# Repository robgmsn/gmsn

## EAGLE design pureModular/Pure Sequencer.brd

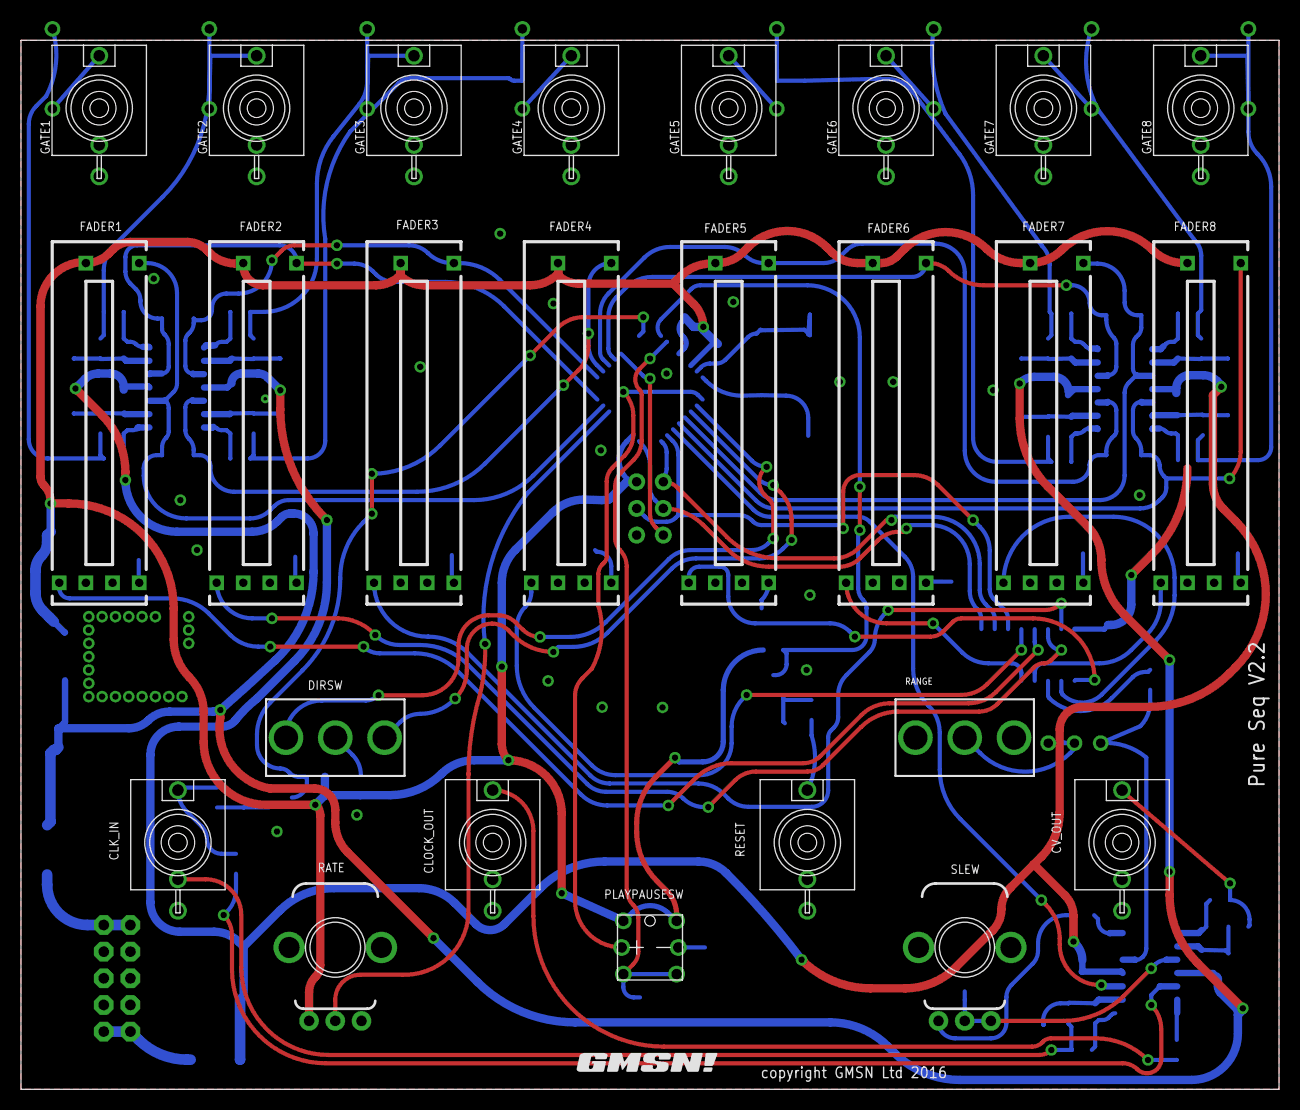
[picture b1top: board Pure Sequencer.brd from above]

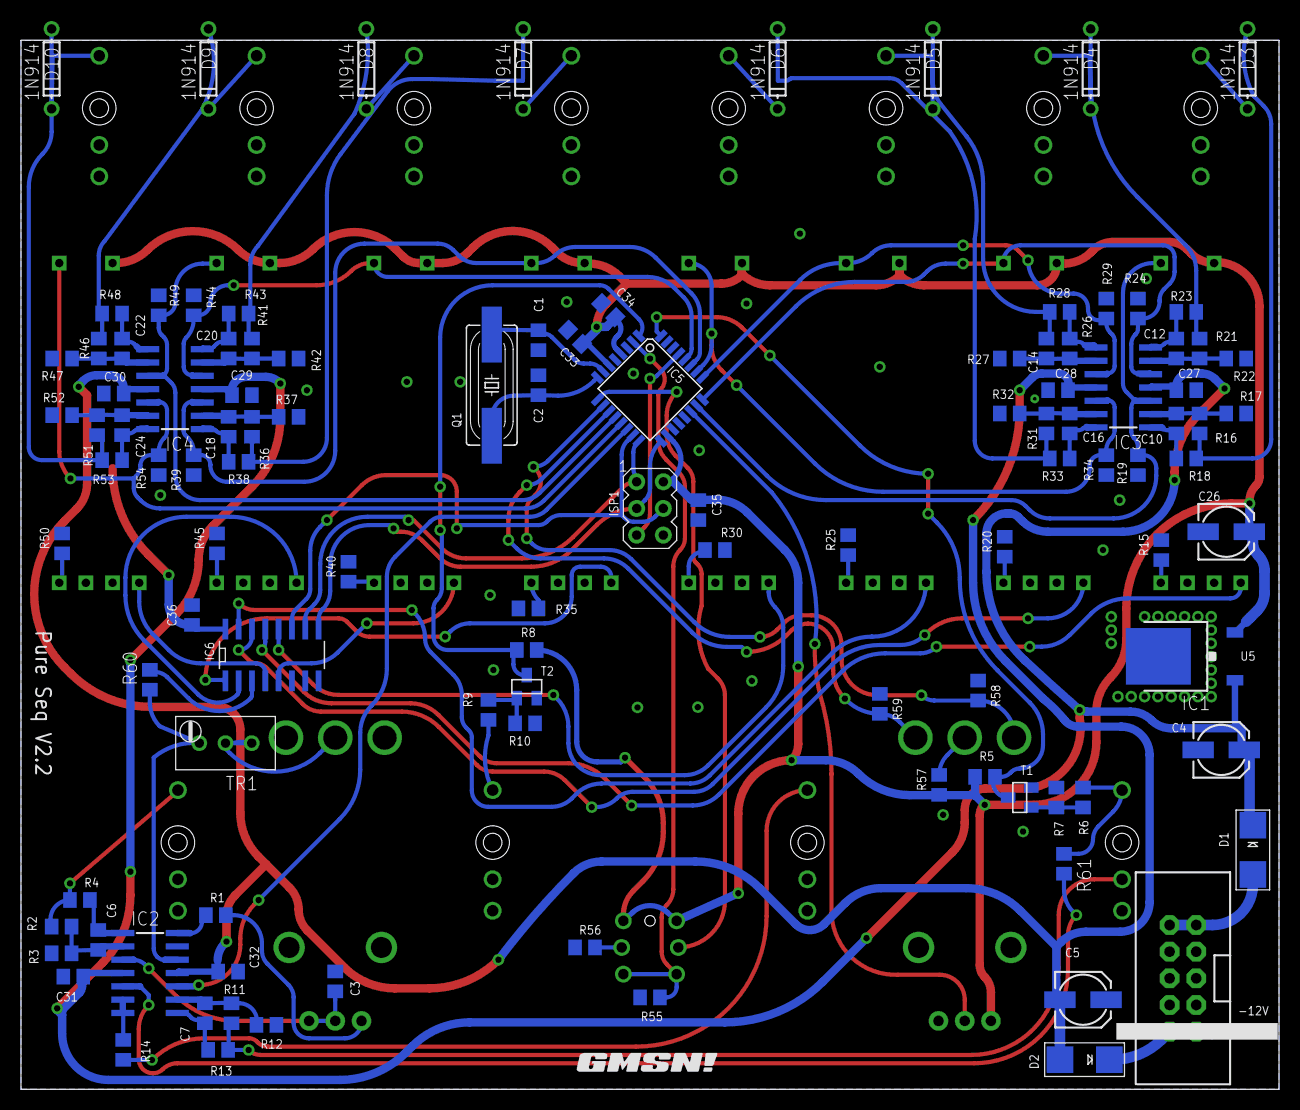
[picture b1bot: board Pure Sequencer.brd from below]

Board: 2 copper layers, 119.9 x 100.0 mm, 136 parts (110 on the bottom side), 97 nets.

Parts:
C1, C2: 22pF; C0805
C3: 1u; C0805
C4, C5, C26: 10uF; 153CLV-0505
C6, C7: 47pF; C0805
C10, C12, C14, C16, C18, C20, C22, C24: 100pF; C0805
C27, C28, C29, C30, C31, C32, C33, C34, C35, C36: 100nF; C0805
CLK_IN: PJ301M-12
CLOCK_OUT: PJ301M-12
CV_OUT: PJ301M-12
D1, D2: STTH102A; SMADIODE
D3, D4, D5, D6, D7, D8, D9, D10: 1N914; DO-41
DIRSW: SWITCH_TOGGLE; TOGGLE_SW
FADER1, FADER2, FADER3, FADER4, FADER5, FADER6, FADER7, FADER8: 100k; FADER_20MM_LED
GATE1, GATE2, GATE3, GATE4, GATE5, GATE6, GATE7, GATE8: PJ301M-12
GLIDE: B100k; POTENTIOMETER_9MM
IC1: BA178M05FP; TO252
IC2, IC3, IC4: TL074; SO14
IC5: ATMEGA328P; TQFP32-08
IC6: CD4051; SOIC_16
ISP1: HEADER2X3-6; AVRISP
JP1: HEADER2X5SHD; 2X5-SHROUDED
Q1: 20MHz; HC49UP
R1, R4: 0R; R0805
R2: 34k; R0805
R3: 56k; R0805
R5, R8: 10k; R0805
R6, R9, R11, R12, R16, R17, R19, R21, R22, R24, R26, R27, R29, R31, R32, R34, R36, R37, R39, R41, R42, R44, R46, R47, R49, R51, R52, R54, R55, R58, R59, R61: 100k; R0805
R7, R10: 1M; R0805
R13, R14, R18, R23, R28, R33, R38, R43, R48, R53, R57: 1k; R0805
R15, R20, R25, R30, R35, R40, R45, R50, R56: 330R; R0805
R60: 200k; R0805
RANGE: SWITCH_TOGGLE; TOGGLE_SW
RATE: B100k; POTENTIOMETER_9MM
RESET: PJ301M-12
SW1: PB6149L
T1, T2: MMBT3904; SOT23
TR1: 100k; TRIMMER_TH
U$1, U$2: GMSN!_LOGO

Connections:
5V: C26.+, C33.1, C34.1, C35.1, C36.1, FADER1.1, FADER2.1, FADER3.1, FADER4.1, FADER5.1, FADER6.1, FADER7.1, FADER8.1, IC1.2, IC5.4, IC5.6, IC5.18, IC6.16, ISP1.2, R5.2, R8.2, R57.1, RATE.P$1, SW1.3, SW1.4
+12V: C4.+, C27.1, C29.1, C31.1, D1.C, IC1.1, IC2.4, IC3.4, IC4.4
-12V: C5.-, C28.2, C30.2, C32.2, D2.A, IC2.11, IC3.11, IC4.11
A: IC5.15, IC6.11, ISP1.4
B: IC5.16, IC6.10, ISP1.1
C: IC5.17, IC6.9, ISP1.3
CLK_IN: IC5.32, R5.1, T1.3
CLK_OUT: IC2.10, IC5.14
G0: FADER1.A, IC3.3, IC5.23, R19.2
G1: FADER2.A, IC3.5, IC5.24, R24.2
G2: FADER3.A, IC3.10, IC5.25, R29.2
G3: FADER4.A, IC3.12, IC5.26, R34.2
G4: FADER5.A, IC4.3, IC5.27, R39.2
G5: FADER6.A, IC4.5, IC5.28, R44.2
G6: FADER7.A, IC4.10, IC5.12, R49.2
G7: FADER8.A, IC4.12, IC5.13, R54.2
GND: C1.2, C2.2, C3.2, C4.-, C5.+, C26.-, C27.2, C28.1, C29.2, C30.1, C31.2, C32.1, C33.2, C34.2, C35.2, C36.2, CLK_IN.GND, CLOCK_OUT.GND, CV_OUT.GND, FADER1.3, FADER2.3, FADER3.3, FADER4.3, FADER5.3, FADER6.3, FADER7.3, FADER8.3, GATE1.GND, GATE2.GND, GATE3.GND, GATE4.GND, GATE5.GND, GATE6.GND, GATE7.GND, GATE8.GND, IC1.3, IC5.3, IC5.5, IC5.21, IC6.6, IC6.7, IC6.8, ISP1.6, JP1.3, JP1.4, JP1.5, JP1.6, JP1.7, JP1.8, R3.1, R7.1, R10.1, R12.2, R15.2, R17.1, R19.1, R20.2, R22.1, R24.1, R25.2, R27.1, R29.1, R30.2, R32.1, R34.1, R35.2, R37.1, R39.1, R40.2, R42.1, R44.1, R45.2, R47.1, R49.1, R50.2, R52.1, R54.1, R55.1, R56.1, R58.1, R59.1, RANGE.3, RATE.P$3, RESET.GND, T1.2, T2.2
unnamed: C1.1, IC5.7, Q1.2
unnamed: C2.1, IC5.8, Q1.1
unnamed: IC2.12, R60.1, TR1.1
unnamed: IC2.13, IC2.14, R1.1
unnamed: GLIDE.P$1, R1.2
unnamed: FADER8.2, IC6.4
unnamed: FADER7.2, IC6.2
unnamed: FADER6.2, IC6.5
unnamed: D1.A, JP1.9, JP1.10
unnamed: D2.C, JP1.1, JP1.2
unnamed: FADER5.2, IC6.1
unnamed: FADER4.2, IC6.12
unnamed: FADER3.2, IC6.15
unnamed: FADER2.2, IC6.14
unnamed: FADER1.2, IC6.13
unnamed: C3.1, GLIDE.P$2, GLIDE.P$3, IC2.3
unnamed: R6.1, R7.2, T1.1
unnamed: IC2.5, R61.2
unnamed: C6.1, IC2.2, R2.1, R3.2
unnamed: C6.2, IC2.1, R4.1
unnamed: CV_OUT.TIP, R2.2, R4.2
unnamed: R9.1, R10.2, T2.1
unnamed: R9.2, RESET.TIP
unnamed: C7.1, IC2.9, R11.2, R12.1
unnamed: C7.2, IC2.8, R13.2
unnamed: CLK_IN.TIP, R6.2, R61.1
unnamed: IC2.6, IC2.7, R14.2
unnamed: CLOCK_OUT.TIP, R14.1
unnamed: CLK_IN.NORM, R11.1, R13.1
unnamed: IC5.22, RATE.P$2
unnamed: FADER1.K, R15.1
unnamed: C10.1, IC3.2, R16.1, R17.2
unnamed: C10.2, IC3.1, R18.1
unnamed: D3.A, R16.2, R18.2
unnamed: FADER3.K, R25.1
unnamed: FADER2.K, R20.1
unnamed: C12.1, IC3.6, R21.1, R22.2
unnamed: C12.2, IC3.7, R23.1
unnamed: D4.A, R21.2, R23.2
unnamed: C14.1, IC3.9, R26.1, R27.2
unnamed: C14.2, IC3.8, R28.1
unnamed: D5.A, R26.2, R28.2
unnamed: FADER4.K, R30.1
unnamed: C16.1, IC3.13, R31.1, R32.2
unnamed: C16.2, IC3.14, R33.1
unnamed: D6.A, R31.2, R33.2
unnamed: FADER5.K, R35.1
unnamed: C18.1, IC4.2, R36.1, R37.2
unnamed: C18.2, IC4.1, R38.1
unnamed: D7.A, R36.2, R38.2
unnamed: FADER6.K, R40.1
unnamed: C20.1, IC4.6, R41.1, R42.2
unnamed: C20.2, IC4.7, R43.1
unnamed: D8.A, R41.2, R43.2
unnamed: FADER7.K, R45.1
unnamed: C22.1, IC4.9, R46.1, R47.2
unnamed: C22.2, IC4.8, R48.1
unnamed: D9.A, R46.2, R48.2
unnamed: FADER8.K, R50.1
unnamed: C24.1, IC4.13, R51.1, R52.2
unnamed: C24.2, IC4.14, R53.1
unnamed: D10.A, R51.2, R53.2
unnamed: IC5.2, R55.2, SW1.1, SW1.2
unnamed: IC5.9, SW1.A
unnamed: R56.2, SW1.K
unnamed: DIRSW.2, R57.2
unnamed: DIRSW.1, IC5.10, R58.2
unnamed: DIRSW.3, IC5.11, R59.2
unnamed: IC6.3, R60.2
unnamed: RANGE.2, TR1.2, TR1.3
unnamed: D6.C, GATE4.TIP
unnamed: D5.C, GATE3.TIP
unnamed: D4.C, GATE2.TIP
unnamed: D3.C, GATE1.TIP
unnamed: D10.C, GATE8.TIP
unnamed: D9.C, GATE7.TIP
unnamed: D8.C, GATE6.TIP
unnamed: D7.C, GATE5.TIP
RESET: IC5.1, R8.1, T2.3
RST: IC5.29, ISP1.5

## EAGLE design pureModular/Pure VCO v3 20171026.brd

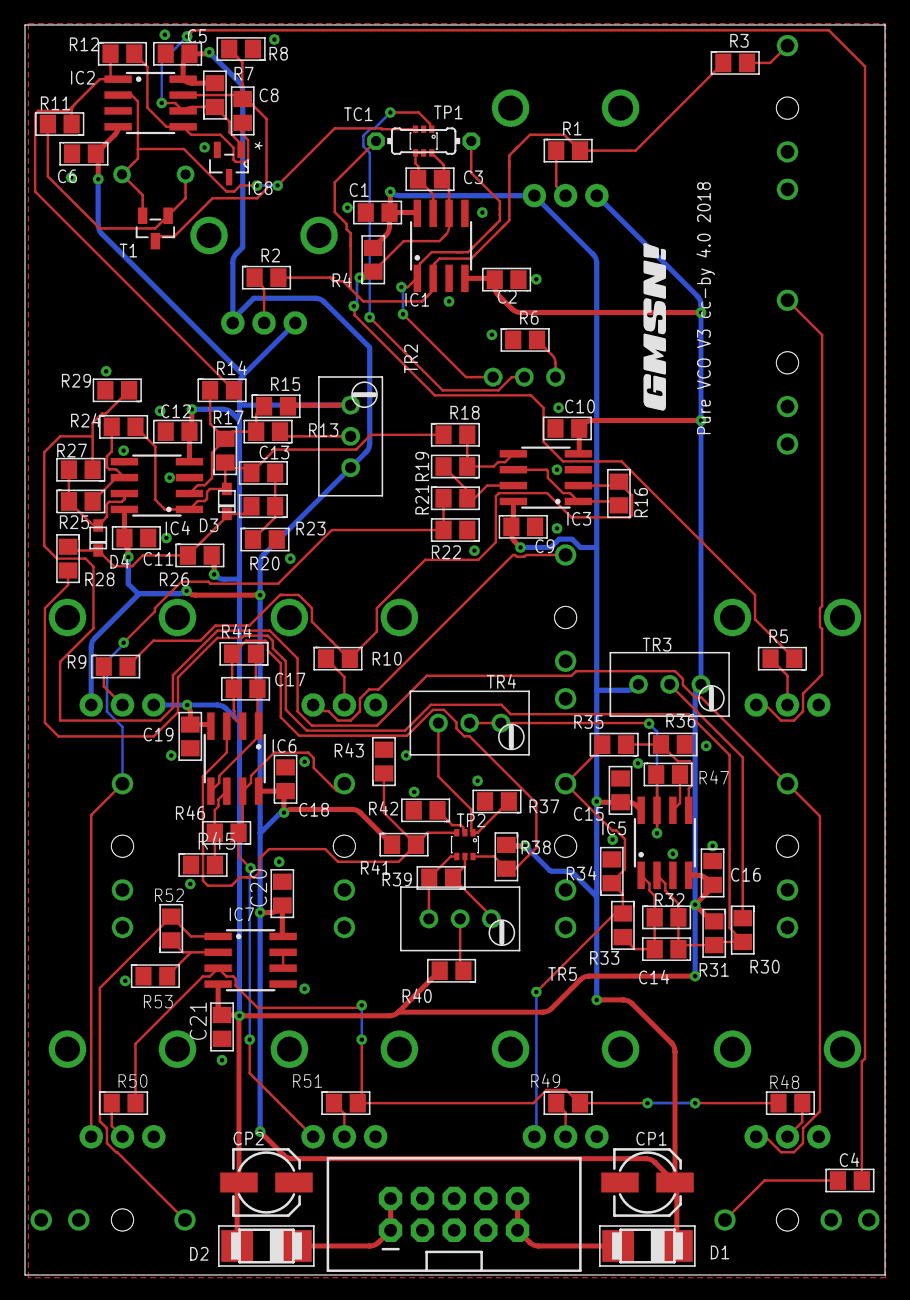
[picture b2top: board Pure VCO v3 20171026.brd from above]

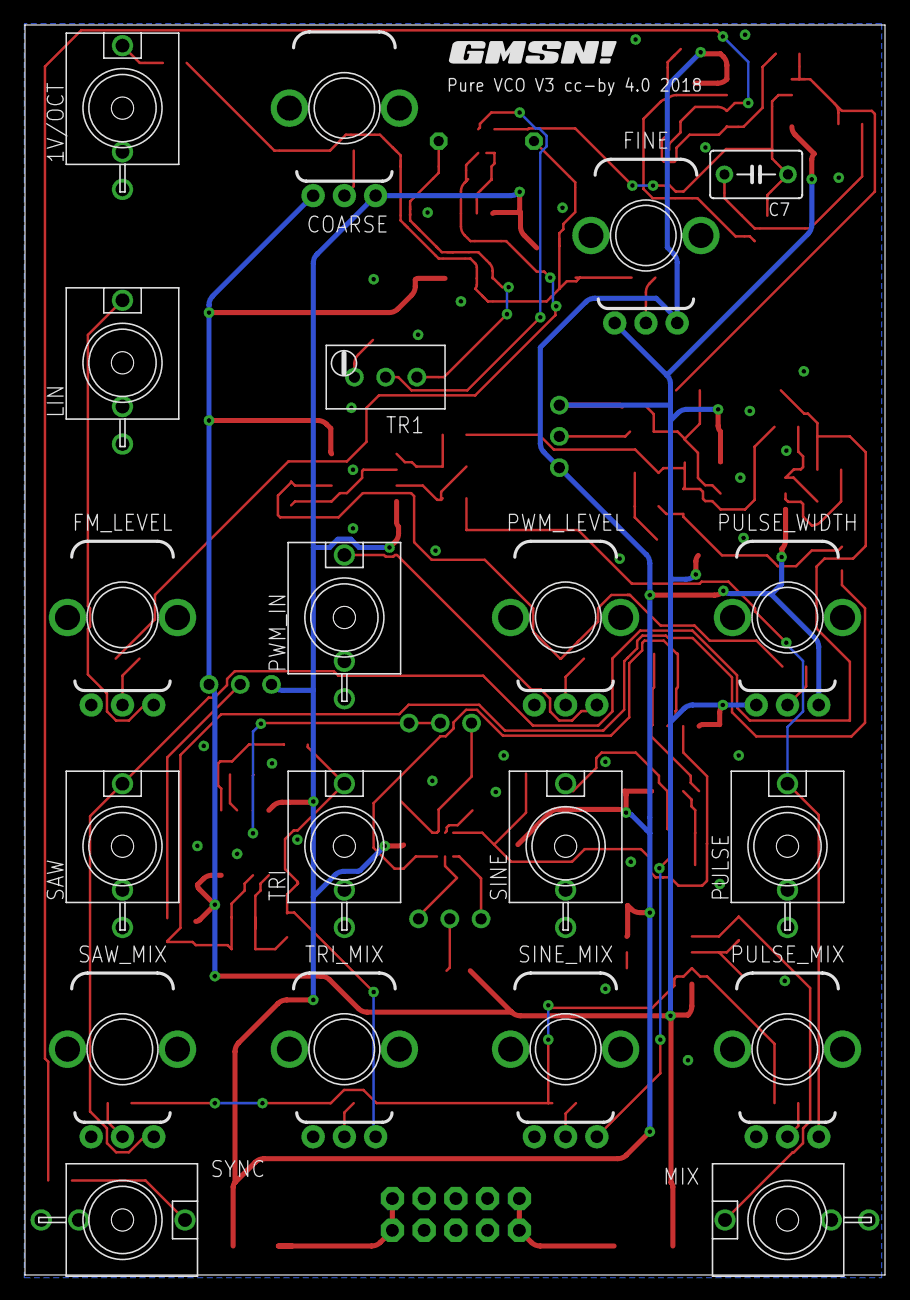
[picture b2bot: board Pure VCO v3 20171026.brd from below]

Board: 2 copper layers, 68.8 x 100.0 mm, 118 parts (21 on the bottom side), 64 nets.

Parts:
1V/OCT: PJ301M-12
C1, C2, C5, C6, C9, C10, C11, C12, C15, C16, C18, C19, C20, C21: 100nF; C0805
C3, C4, C17: 100pF; C0805
C7: 2.2nF; POLY_CAP
C8: 22pF; C0805
C13: 10nF; C0805
C14: 1nF; C0805
COARSE: B100k; POTENTIOMETER_9MM
CP1, CP2: 10uF; 153CLV-0505
D1, D2: STTH102A; SMADIODE
D3, D4: 1N914; SOD-323F
FINE: B100k; POTENTIOMETER_9MM
FM_LEVEL: B100k; POTENTIOMETER_9MM
IC1, IC2, IC3, IC4, IC5, IC6, IC7: TL072; SO08
IC8: LM4040A50IDBZT; SOT95P237X112-3N
JP1: HEADER2X5SHD; 2X5-SHROUDED
LIN: PJ301M-12
MIX: PJ301M-12
PULSE: PJ301M-12
PULSE_MIX: B100k; POTENTIOMETER_9MM
PULSE_WIDTH: B100k; POTENTIOMETER_9MM
PWM_IN: PJ301M-12
PWM_LEVEL: B100k; POTENTIOMETER_9MM
R1: 150k; R0805
R2: 2M2; R0805
R3, R16, R30, R48, R49, R50, R51, R52, R53: 100k; R0805
R4, R19: 2M; R0805
R5: 560k; R0805
R6: 390R; R0805
R7: 87k; R0805
R8, R36: 3k3; R0805
R9: 120k; R0805
R10, R17: 39k; R0805
R11: 680R; R0805
R12: 9k1; R0805
R13: 5k6; R0805
R14, R20, R23, R28, R38, R40, R41, R43, R44, R45: 10k; R0805
R15: 56k; R0805
R18: 2k2; R0805
R21, R22: 1k5; R0805
R24, R25: 22k; R0805
R26, R32, R46: 19k1; R0805
R27, R29, R34, R37, R42: 2k; R0805
R31: 27k; R0805
R33, R35, R47: 1k3; R0805
R39: 402R; R0805
SAW: PJ301M-12
SAW_MIX: B100k; POTENTIOMETER_9MM
SINE: PJ301M-12
SINE_MIX: B100k; POTENTIOMETER_9MM
SYNC: PJ301M-12
T1: MMBFJ309; N_CHN
TC1: 2k; 0204/7
TP1, TP2: DMMT3904W-7-F; TRANS_PAIR
TR1: 100R; TRIMMER_TH
TR2, TR3, TR4, TR5: 100k; TRIMMER_TH
TRI: PJ301M-12
TRI_MIX: B100k; POTENTIOMETER_9MM
U$1, U$2: GMSN!_LOGO

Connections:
+12V: C1.1, C5.1, C9.1, C11.1, C15.1, C18.1, C20.1, COARSE.P$3, CP1.+, D1.C, FINE.P$3, IC1.8, IC2.8, IC3.8, IC4.8, IC5.8, IC6.8, IC7.8, PULSE_WIDTH.P$3, R4.2, R7.2, R38.1, R41.1, TR2.3, TR3.3
-12V: C2.2, C6.2, C10.2, C12.2, C16.2, C19.2, C21.2, COARSE.P$1, CP2.-, D2.A, FINE.P$1, IC1.4, IC2.4, IC3.4, IC4.4, IC5.4, IC6.4, IC7.4, PULSE_WIDTH.P$1, R15.2, R26.2, R31.1, R40.2, TR2.1, TR3.1
GND: 1V/OCT.GND, 1V/OCT.NORM, C1.2, C2.1, C5.2, C6.1, C9.2, C10.1, C11.2, C12.1, C15.2, C16.1, C18.2, C19.1, C20.2, C21.1, CP1.-, CP2.+, FM_LEVEL.P$1, IC1.3, IC1.5, IC2.3, IC3.3, IC4.3, IC4.5, IC5.3, IC7.5, IC8.2, JP1.3, JP1.4, JP1.5, JP1.6, JP1.7, JP1.8, LIN.GND, LIN.NORM, MIX.GND, PULSE.GND, PULSE_MIX.P$1, PWM_IN.GND, PWM_LEVEL.P$1, R6.1, R8.1, R20.2, R22.1, R29.2, R34.2, R36.2, R37.2, R42.2, R43.2, R45.1, R53.1, SAW.GND, SAW_MIX.P$1, SINE.GND, SINE_MIX.P$1, SYNC.GND, TP1.B1, TRI.GND, TRI_MIX.P$1
unnamed: D1.A, JP1.9, JP1.10
unnamed: COARSE.P$2, R1.1
unnamed: D2.C, JP1.1, JP1.2
unnamed: IC1.2, R1.2, R2.2, R3.1, TC1.1
unnamed: FINE.P$2, R2.1
unnamed: IC3.1, IC3.6, R16.2
unnamed: IC1.1, TC1.2, TR1.3
unnamed: R6.2, TR1.1
unnamed: 1V/OCT.TIP, R3.2
unnamed: TP1.B2, TR1.2
unnamed: C7.2, R11.2, T1.D
unnamed: C3.1, IC1.6, R4.1, R5.1, TP1.C2
unnamed: C7.1, IC2.2, T1.S, TP1.C1
unnamed: C17.1, IC6.2, R38.2, R44.2, TP2.C2
unnamed: FM_LEVEL.P$3, LIN.TIP
unnamed: C8.1, IC2.5, R12.2
unnamed: FM_LEVEL.P$2, R5.2
unnamed: C3.2, IC1.7, TP1.E1, TP1.E2
unnamed: IC5.6, R47.2
unnamed: C8.2, IC2.7, R8.2, T1.G
unnamed: C4.1, SYNC.TIP
unnamed: C4.2, IC2.6, IC8.1, R7.1
unnamed: R13.1, TR2.2
unnamed: IC4.2, R13.2, R14.1, R15.1, R17.2
unnamed: IC7.6, IC7.7
unnamed: C13.2, R20.1, R23.1
unnamed: R30.1, TR3.2
unnamed: IC4.6, R24.1, R25.2
unnamed: D4.A, IC4.7, R25.1, R27.2
unnamed: D3.C, D4.C, R23.2, R26.1, R28.1
unnamed: C14.1, IC5.2, R28.2, R30.2, R31.2, R32.2
unnamed: IC7.3, R48.2, R49.2, R50.2, R51.2
unnamed: IC3.5, R18.2, R19.1
unnamed: C14.2, IC5.1, R32.1, R33.2
unnamed: R48.1, SAW_MIX.P$2
unnamed: IC3.7, R19.2, R21.2
unnamed: PULSE_WIDTH.P$2, R9.1
unnamed: PWM_IN.TIP, PWM_LEVEL.P$3
unnamed: IC3.2, R9.2, R10.2, R16.1
unnamed: R49.1, TRI_MIX.P$2
unnamed: PULSE_MIX.P$2, R50.1
unnamed: R51.1, SINE_MIX.P$2
unnamed: PWM_LEVEL.P$2, R10.1
unnamed: IC7.2, R52.1, R53.2
unnamed: IC7.1, MIX.TIP, R52.2
unnamed: IC5.7, R47.1, TR4.1, TR4.2
unnamed: R37.1, TP2.B2, TR4.3
unnamed: R39.1, TP2.E2, TR5.1
unnamed: R39.2, TP2.E1, TR5.3
unnamed: R40.1, TR5.2
unnamed: R42.1, TP2.B1
unnamed: IC6.3, R41.2, R43.1, TP2.C1
unnamed: IC5.5, R35.1, R36.1
unnamed: IC6.6, R45.2, R46.2
PULSE: PULSE.TIP, PULSE_MIX.P$3, R21.1, R22.2
PULSEIN: C13.1, D3.A, IC4.1, R17.1, R18.1, R24.2
SAW: R27.1, R29.1, SAW.TIP, SAW_MIX.P$3
SAWCORE: IC2.1, R11.1, R12.1, R14.2
SINE: IC6.7, R46.1, SINE.TIP, SINE_MIX.P$3
SINE_PRE1: C17.2, IC6.1, IC6.5, R44.1
TRI: R33.1, R34.1, R35.2, TRI.TIP, TRI_MIX.P$3

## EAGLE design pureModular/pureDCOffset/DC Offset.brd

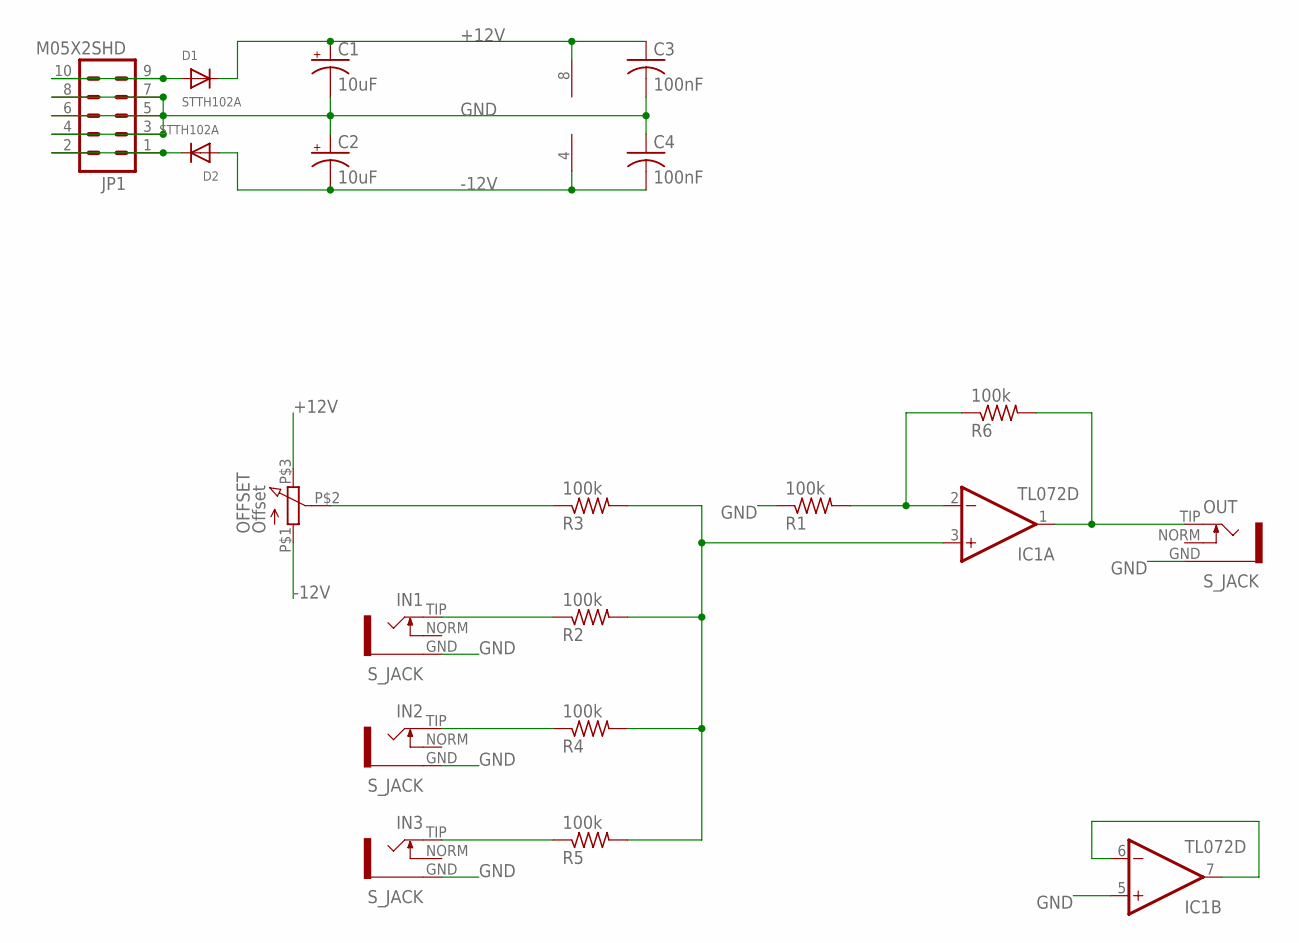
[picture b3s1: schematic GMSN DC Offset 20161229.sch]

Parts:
C1, C2: 10uF; 153CLV-0505
C3, C4: 100nF; C0805
D1, D2: STTH102A; SMADIODE
IC1: TL072D; SO08
IN1, IN2, IN3: S_JACK
JP1: M05X2SHD; 2X5-SHROUDED
OFFSET: Offset; Q-POT
OUT: S_JACK
R1, R2, R3, R4, R5, R6: 100k; R0805

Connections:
+12V: C1.+, C3.1, D1.C, IC1.8 (V+), OFFSET.P$3 (3)
-12V: C2.-, C4.2, D2.A, IC1.4 (V-), OFFSET.P$1 (1)
GND: C1.-, C2.+, C3.2, C4.1, IC1.5 (+IN), IN1.GND, IN2.GND, IN3.GND, JP1.3, JP1.4, JP1.5, JP1.6, JP1.7, JP1.8, OUT.GND, R1.1
unnamed: D1.A, JP1.9, JP1.10
unnamed: OFFSET.P$2 (2), R3.1
unnamed: IC1.3 (+IN), R2.2, R3.2, R4.2, R5.2
unnamed: D2.C, JP1.1, JP1.2
unnamed: IC1.2 (-IN), R1.2, R6.1
unnamed: IC1.1 (OUT), OUT.TIP, R6.2
unnamed: IC1.6 (-IN), IC1.7 (OUT)
unnamed: IN1.TIP, R2.1
unnamed: IN2.TIP, R4.1
unnamed: IN3.TIP, R5.1

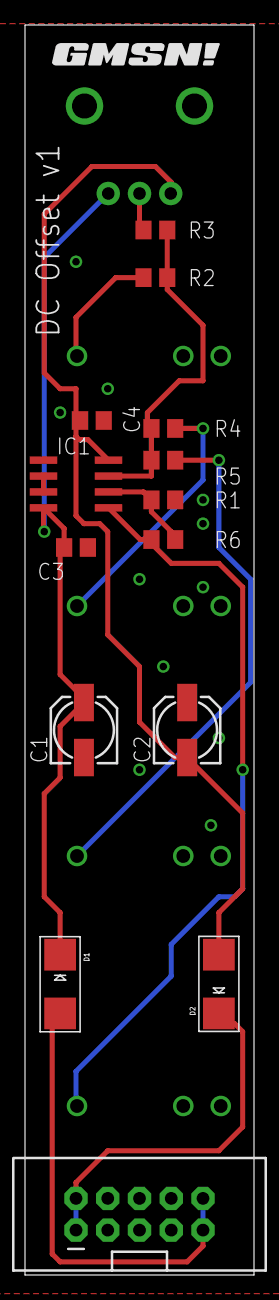
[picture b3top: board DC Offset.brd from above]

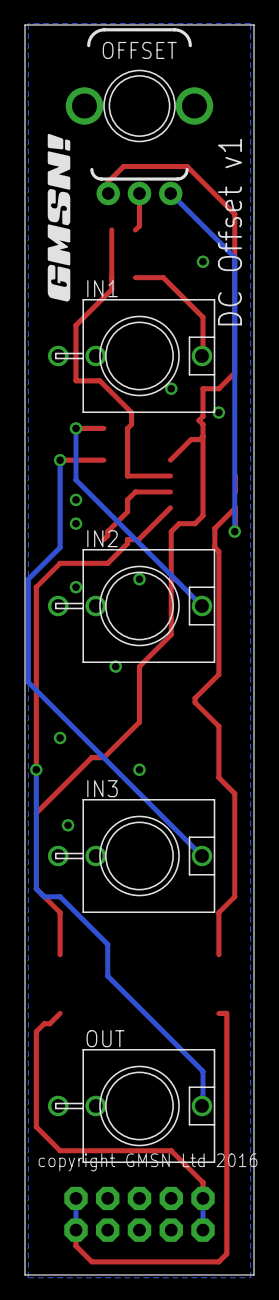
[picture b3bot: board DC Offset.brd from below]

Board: 2 copper layers, 18.3 x 100.0 mm, 21 parts (6 on the bottom side), 13 nets.

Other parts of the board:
U$1, U$2: GMSN!_LOGO

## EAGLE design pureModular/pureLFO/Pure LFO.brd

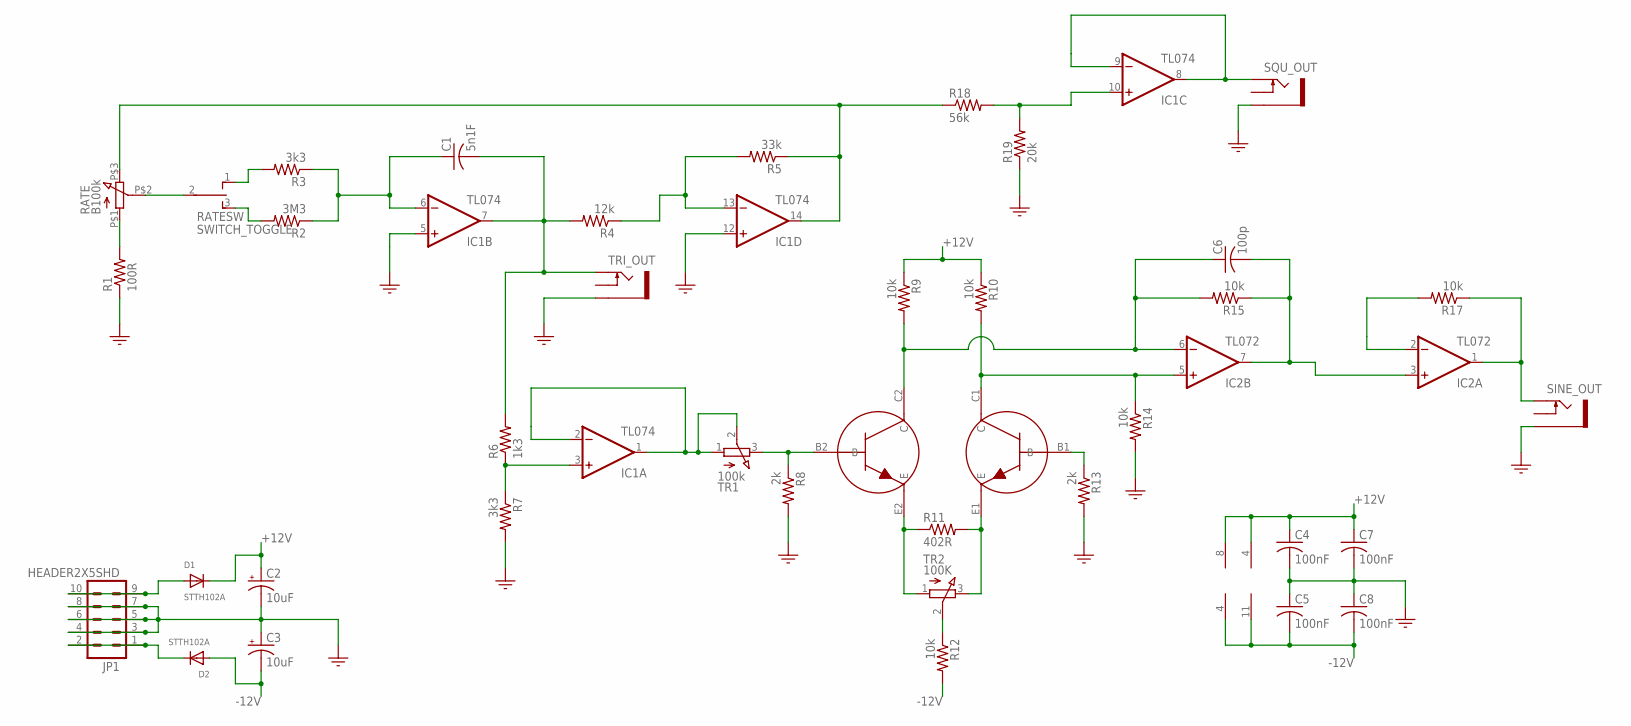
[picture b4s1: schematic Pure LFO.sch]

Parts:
C1: 5n1F; C0805
C2, C3: 10uF; 153CLV-0505
C4, C5, C7, C8: 100nF; C0805
C6: 100p; C0805
D1, D2: STTH102A; SMADIODE
IC1: TL074; SO14
IC2: TL072; SO08
JP1: HEADER2X5SHD; 2X5-SHROUDED
R1: 100R; R0805
R2: 3M3; R0805
R3, R7: 3k3; R0805
R4: 12k; R0805
R5: 33k; R0805
R6: 1k3; R0805
R8, R13: 2k; R0805
R9, R10, R12, R14, R15, R17: 10k; R0805
R11: 402R; R0805
R18: 56k; R0805
R19: 20k; R0805
RATE: B100k; POTENTIOMETER_9MM
RATESW: SWITCH_TOGGLE; TOGGLE_SW
SINE_OUT: SOCKET_MONO_3.5MMPJ301M-12; PJ301M-12
SQU_OUT: SOCKET_MONO_3.5MMPJ301M-12; PJ301M-12
T3: DMMT3904W-7-F; TRANS_PAIR
TR1: 100k; TRIMMER_TH
TR2: 100K; TRIMMER_TH
TRI_OUT: SOCKET_MONO_3.5MMPJ301M-12; PJ301M-12

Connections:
+12V: C2.+, C4.1, C7.1, D1.C, IC1.4 (V+), IC2.8 (V+), R9.1, R10.1
-12V: C3.-, C5.2, C8.2, D2.A, IC1.11 (V-), IC2.4 (V-), R12.2
GND: C2.-, C3.+, C4.2, C5.1, C7.2, C8.1, IC1.5 (+IN), IC1.12 (+IN), JP1.3, JP1.4, JP1.5, JP1.6, JP1.7, JP1.8, R1.1, R7.2, R8.2, R13.2, R14.2, R19.1, SINE_OUT.GND (SLEEVE), SQU_OUT.GND (SLEEVE), TRI_OUT.GND (SLEEVE)
unnamed: R1.2, RATE.P$1 (1)
unnamed: RATE.P$2 (2), RATESW.2
unnamed: R3.2, RATESW.1 (O)
unnamed: R2.2, RATESW.3 (S)
unnamed: IC1.10 (+IN), R18.2, R19.2
unnamed: C1.1, IC1.6 (-IN), R2.1, R3.1
unnamed: C1.2, IC1.7 (OUT), R4.2, R6.2, TRI_OUT.TIP
unnamed: IC1.8 (OUT), IC1.9 (-IN), SQU_OUT.TIP
unnamed: IC1.13 (-IN), R4.1, R5.2
unnamed: D1.A, JP1.9, JP1.10
unnamed: IC1.14 (OUT), R5.1, R18.1, RATE.P$3 (3)
unnamed: R11.1, T3.E2 (E), TR2.1
unnamed: R8.1, T3.B2 (B), TR1.3
unnamed: R11.2, T3.E1 (E), TR2.3
unnamed: R12.1, TR2.2
unnamed: R13.1, T3.B1 (B)
unnamed: C6.1, IC2.6 (-IN), R9.2, R15.2, T3.C2 (C)
unnamed: IC1.1 (OUT), IC1.2 (-IN), TR1.1, TR1.2
unnamed: IC2.5 (+IN), R10.2, R14.1, T3.C1 (C)
unnamed: IC1.3 (+IN), R6.1, R7.1
unnamed: IC2.2 (-IN), R17.2
unnamed: D2.C, JP1.1, JP1.2
SINE: IC2.1 (OUT), R17.1, SINE_OUT.TIP
SINE_PRE: C6.2, IC2.3 (+IN), IC2.7 (OUT), R15.1

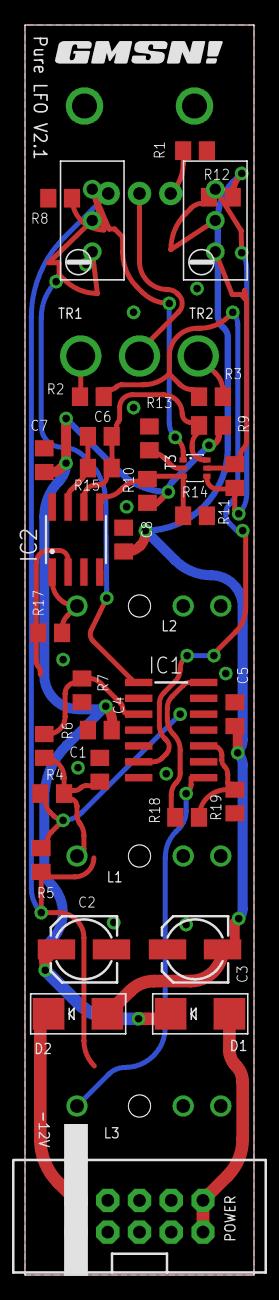
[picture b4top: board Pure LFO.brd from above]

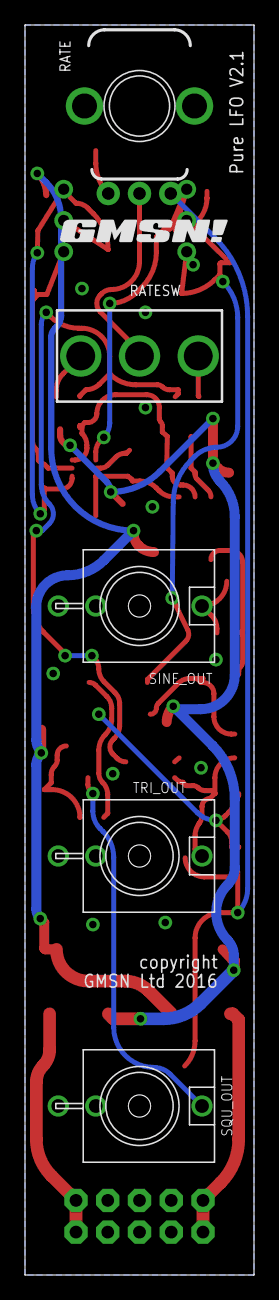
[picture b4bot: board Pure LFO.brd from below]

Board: 2 copper layers, 18.3 x 100.0 mm, 41 parts (6 on the bottom side), 27 nets.

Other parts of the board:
U$1, U$2: GMSN!_LOGO

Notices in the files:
pureModular/Pure Sequencer.brd:
copyright GMSN Ltd 2016
pureModular/Pure VCO v3 20171026.brd:
Pure VCO V3 cc-by 4.0 2018
